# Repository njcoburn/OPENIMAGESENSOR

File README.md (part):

# Open Image Sensor

**Current — completed results checkpoint, 4 October:** all 18 selected
five-device bank cases passed, with 36 transients and 3,456 reference calculations.
The sequence finished 2 October at 15:11 Pacific after 48 h 21 min; no verification
jobs remain active. Worst total/tracking errors are 456.591/215.322 µV against
500 µV; sample refinement is 0.465218 µV against 10 µV. This is selected coverage
of a one-row, 64-column bank, not full-chip qualification.
Next: define bounded supply/wiring/placement checks before real drivers and
multirow integration. [Resume here](PICK_UP_HERE.md) ·
[Completion record](simulations/stack5-completion-checkpoint-20261004.json) ·
[Overview](docs/overview.html#stack5-completion).
Earlier status entries below are historical.

**Latest review, 30 September — stopped; no active simulations:** all three
100 ns runs and 576 references completed and are independently audited. All three
50 ns runs hit the four-hour timeout, leaving 11 of 384 output samples unverified.
Coarse typical/SS totals are 391.959/445.375 µV, but FF is 602.413 µV against
500 µV. 7 available fine FF samples also exceed the limit (up to 577.376 µV).
No complete pair is qualified and the later queue did not start. Next: address
remaining fast-corner capture/storage error and use a longer watchdog for reruns.
[Reviewed evidence](docs/overview.html#stack3-interrupted-review) · [Handoff](PICK_UP_HERE.md).
Earlier running/completion statements below are historical.

**Running, 30 September — 64-column candidate sequence:** checkpoint and
changelog were pushed as `06889e5` before this work. The new physical 64-column
bank passes DRC/LVS and all capture-chain checks. Six typical/SS/FF 125 °C
simulations are running, with 576 matched references planned for this batch.
On audited passes, the controller advances through mixed corners, 27 °C cases,
and remaining typical-process illumination patterns (18 cases / 36 transients /
3,456 references in the complete queue). Failure stops subsequent stages.
[Live overview](docs/overview.html#stack3-sequence) · [Status](build/stack3-sequence-20260930-away/status.json).
Earlier status entries below are historical.

**Latest, 30 September — physical candidate verified:** the three-device capture
switch is implemented in a separate column and two-column bank. DRC/LVS and
40 µm abutment pass. With 12.5 µs acquisition, extracted typical/SS/FF worst total
errors are 152.197/181.071/258.782 µV across port/far placement (limit 500 µV).
Placement sensitivity is below 0.044 µV. This stage completed 18 transients and
108 references. Next: separate 64-column candidate build and process validation.
No simulation jobs remain active; the old 64-column checkpoint is unchanged.
[Physical candidate and rerun guide](docs/overview.html#physical-stack3) · [Handoff](PICK_UP_HERE.md).
Earlier status entries below are historical.

**Latest, 30 September — candidate cycle tests reviewed:** 20 transients and
120 references are complete. Three series NMOS capture devices pass the selected
two-column typical/SS/FF screen; FF error improves from 1240.756 to 410.653 µV
(limit 500 µV). A separate 12.5 µs acquisition test improves SS settling.
Next: check the combined changes, implement a separate physical column revision,
verify extraction/DRC/LVS and small-bank behavior, then repeat full-bank corners.
The current GDS and its known process failures remain unchanged. No jobs are active.
[Results and rerun guide](docs/overview.html#bank-capture-cycles) · [Handoff](PICK_UP_HERE.md).
Earlier status entries below are historical.

**Diagnosis completed, 30 September:** the process failures are reviewed and
short current/candidate tests are complete. FF retention is dominated by the
NMOS capture switch in the probed states; series devices reduce DC leakage but
are not yet a validated correction. Next: candidate capture/readout transients
and an SS acquisition-timing test. No new long batch is active.
[Diagnosis and plots](docs/overview.html#bank-process-diagnosis) · [Handoff](PICK_UP_HERE.md).

**Current, 30 September:** the SS/FF process batch finished. Both total-error
checks fail (512.924 / 2000.323 µV vs 500 µV); other selected checks pass. All
384 references are audited and 1,740 evidence files verify. Next is diagnosis
of SS output settling and FF storage retention, before more corner coverage.
[Review](simulations/compact-bank-process-review-20260930.json) · [Handoff](PICK_UP_HERE.md).
Earlier active-job descriptions below are historical.

**Active, 30 September:** the first SS/FF MOS-process batch is running at
125 °C inverse illumination: four 100/50 ns transients and 384 planned references,
with an independent watcher. The small FF control failed capture/storage accuracy;
that failure is retained while measuring the actual 64-column layout. Results
are pending. [Overview journal](docs/overview.html#verification-journal) ·
[Profile and scope](verification/compact-bank-process-suite.json) · [Handoff](PICK_UP_HERE.md).

[Verification journal and rerun guide](docs/verification-journal.html) explains every test, records results and tracks what is needed for repeatable pixel-layout experiments.

**Completed and reviewed, 30 September:** bright illumination and the authorized
joint parasitic-placement batch both pass. All five illumination patterns now
pass at 27/125 °C: 20 transients and 1,920 independent references, plus four
placement transients and 384 references. Those baseline jobs are complete; the process batch above is active.
Next: process/wire/supply corners and remaining placement/local-supply checks,
then real drivers and repeated rows. Full-chip qualification remains open.
[Completion review](simulations/compact-bank-overnight-review-20260930.json) · [Handoff](PICK_UP_HERE.md).

**Current goal: 64×64 first silicon on wafer.space GF180, with modest frame rate.**
[Completion plan](COMPLETION_PLAN.md) · [Next steps](NEXT_STEPS.md) · [Handoff](PICK_UP_HERE.md)

**Overnight results:** bright total error is 359.158/402.995 µV at 27/125 °C
against 500 µV. Joint relocation of 67 conserved shunts passes at 27 °C
alternating and 125 °C inverse; the largest HOLD/STORE change is 1.527 µV
against 10 µV. Bright and placement took 3.97 and 3.87 hours respectively,
including audits. All ten simulation/audit containers exited successfully.

**Completed and reviewed, 29 September:** uniform dark passes at 27/125 °C:
248.852/411.912 µV worst total error against 500 µV, with four completed transients
and 384 audited references. The batch finished in 4.04 hours. Nothing from this
batch is still running; middle and bright have also passed as described above.
[Uniform results](docs/overview.html#compact-bank-64-uniform).

[View the current device layout](docs/overview.html#current-device-layout) — labeled
GDS and close-up of the implemented 64-column bank plus one pixel row, measuring
2.668 × 1.070 mm. [Exact GDS checkpoint](checkpoints/compact-bank-64-matrix/README.md).
The full 64×64 chip remains to be assembled.

**Latest, reviewed 29 September:** the complete alternating/inverse matrix now
**passes at both 27 °C and 125 °C**. The new 27 °C inverse / 125 °C alternating
cases reach 387.179/430.383 µV worst total error, below 500 µV. All eight matrix
transients and 768 references are audited; maximum saved-sample refinement is
0.150 µV, below 10 µV. All 1,707 distinct new evidence files verify. The jobs and
auditor finished successfully; the completed uniform-dark batch is described above.
[Temperature/pattern matrix](docs/overview.html#compact-bank-64-cross)

**Completed, 28 September:** both earlier complete 64-column bank screens **pass**.
All four transients finish 128 reads each, with 384 independently audited references
across the nominal alternating and hot inverse cases. Worst total error is
**372.606 µV at 27 °C / 438.213 µV at 125 °C**, below 500 µV; maximum saved-sample
100/50 ns difference is **0.133 µV**, below 10 µV. All 1,711 distinct evidence
files verified. The jobs and auditor have finished successfully.

All five illumination patterns at both temperatures now pass. Remaining
corner/placement coverage precedes real drivers and repeated rows.
Full-chip qualification remains open.
[Results and plots](docs/overview.html#compact-bank-64-full) · [Current handoff](PICK_UP_HERE.md)

**Previous electrical results, 27 September:**

The [16-column extension](docs/overview.html#compact-bank-16-extension) passes
its selected checks across **46 transients and 1,152 references**. Worst total
error is 433.171 µV and tracking is 301.667 µV
(500 µV limits). All five patterns at 27/125 °C have 100/50 ns comparisons;
the largest saved-terminal difference is 0.450 µV. All 19 individual
shunts plus their joint placement pass for the hot inverse pattern, with
0.105/0.137 µV maximum HOLD/STORE changes (10 µV limit). The separate
inverse-pattern layout–schematic response reaches 10.062 mV and has
no assigned acceptance threshold.

The 8 µm bus alone does not solve 64-column scaling: a matched column-62
readout fails at 1,994.440 µV total error. A new physical distributed ground
return **fails with 10 µs acquisition** at 547.178 µV total error and
340.253 µV tracking. Both main DRC checks and both LVS paths pass, and
a geometry audit restricts the change to ground metal/vias. The new bank is
2667.87 × 1069.80 µm, within the 2700 × 1100 µm budget. See the
[selected readout comparison](docs/overview.html#compact-bank-64-read-probes)
and [capture/ground diagnosis](docs/compact-bank-64-ground8.md).

Extending acquisition from 10 to 12 µs on that same grid **passes the selected
diagnostic** at 269.281 µV total error and 62.529 µV tracking. Only the
ACQ falling edges and sample times move; selection/reset and the 20 µs slot
budget stay unchanged. Three new matched references and an unchanged-prefix
comparison are audited. The separately versioned full-bank runner now supports
this timing. The original attempts were stopped on 27 September; the resumed
nominal/hot inverse pairs now pass their complete selected audits. See
PICK_UP_HERE.md for results and the next coverage batch.

These are bounded development screens. Full 16-column corner/placement
coverage, remaining full-bank corners/individual placements, real drivers, repeated rows
and exact 64×64 manufacturing qualification remain open.

**Original geometry constraint:** the older array and bank do not fit a standard
full slot. The compact pixel/bank work above addresses that block-size constraint. The new 40 µm-pitch
[floorplan budget](docs/64x64-slot-fit.md) fits the published default core as
planning rectangles; it is not qualified GDS. The full 64×64 chip is not yet assembled.

The extracted 64-pixel row and isolated physical capture column have passing
electrical evidence. The physical bank passes scoped DRC/LVS, but coupled
readout, multirow operation, real drivers and final-chip signoff remain open.
Docker access is restored. The new [40 µm compact pixel](docs/compact-pixel.md)
and 2×2 control pass main DRC and both LVS paths; the 2×2 nominal/hot electrical
screens and timestep checks pass. The [reset follow-up](docs/compact-reset.md)
passes 12 transients and extended references using audited shunt placements;
the raw isolated extraction remains diagnostic. The original raw/reduced full-bank
initialization timed out in four bounded controls before the later KLU
continuation resolved startup. The new [compact capture column](docs/compact-capture.md) fits 40 µm
pitch and passes scoped DRC/LVS, adjacent-column spacing, 60 transients and
36 references. The [physically joined tile](docs/compact-tile.md) now passes
54 transients and 72 references, with 419.404 µV worst total capture/readout
error. The [shared two-column bank](docs/compact-bank.md) now passes both main
DRC/LVS paths, 100 transients and 240 references (419.033 µV worst total error).
It includes physical reference MOS and shared buses; the later 1×64 work is above.
The separate layout–schematic integrated-response difference reaches 5.821 mV.
A separate
3×3 tapeout is not a prerequisite.

## Earlier development checkpoints

The dated entries below retain earlier evidence and historical release targets.
Use the completion plan above for current priorities.

**Latest physical result:** Reinforced supply/reference and local buffer routing passes both main DRC checks and both LVS paths. Worst nominal/hot static buffer shift across 1.2–2.0 V falls from **5.331 to 1.320 mV**; all 16 selected DC controls complete. The coupled reset test still times out during initialization; full readout remains unqualified. [Measured comparison and tradeoffs](docs/bank-reinforcement.md).

**Earlier physical result:** The shared 64-column capture bank passes Magic/KLayout main DRC and both LVS paths: 450 MOS devices, 512 storage plates and fully extracted shared routing. Isolated DC controls reveal millivolt-scale spatial shifts; coupled-row accuracy is not yet qualified. [Bank measurements and scope](docs/capture-bank.md).

**Earlier diagnosis:** Eight DC controls implicate VDD/PREF routing in the spatial spread; idealizing supplies/references still leaves a 2.199 mV common offset. Full readout qualification remains open. [Measured controls and reset diagnostics](docs/bank-routing.md).

**Earlier isolated-column result:** The isolated capture/readout column passes all 48 nominal/hot simulations, Magic/KLayout main DRC and both LVS paths. Worst tracking error is 176.560 µV (limit 500); timestep difference is 0.318 µV (limit 10). Shared-bank results are above. [Qualification and scope](docs/capture-column-qualification.md).

**Latest full-row result:** Full 64-column readout on the physical power grid passes at 27/125 °C: 173.457/289.658 µV total output error (limit 500) and 3.897/3.703 µV timestep difference (limit 10). Pixel/row wiring uses extracted R+C; physical storage/periphery, multirow operation and startup remain open. [Results](docs/grid-readout.md) · [Next physical tile](docs/capture-tile-plan.md).

**Earlier grid result:** A physical upper-metal row power grid reduces turn-on VDD loss from 354.35 to 42.57 mV, with passing layout/connectivity checks and nominal edge refinement. Nominal/hot runs complete through capture at about 4.09 mV wiring loss. The full serial-output follow-up is now complete; see the latest result above. [Measurements and scope](docs/row-power.md).

**Earlier capture result:** The revised 64-column capture circuit passes nominal/hot accuracy and timestep checks: 171.295/289.919 µV total error, below 500 µV. It removes the measured serial-exposure gradient in these tests. Physical capacitors, distributed power and peripheral routing remain the next stage; startup/full-chip/tapeout qualification is open. [Results and exact scope](docs/array-recovery.md).

**Earlier strip result:** Extracted 1×64/64×1 tests exposed supply drop, exposure skew and late bright-pixel saturation. The original serial mode's numerical refinement remains unqualified. [Original measurements](docs/array-strips.md).

**Earlier interface result:** The proposed heavy-load interface completes three frames at 0.461 mV tracking error. Explicit unused-pad terminations allow both cold cases to run, including a selected three-frame/refinement check. These are conditional proposals, not released hardware. [Results](docs/readout-followup.md) · [Are we ready for tapeout or a larger array?](docs/tapeout-readiness.md).

**Earlier load/corner screen:** Five initial load/corner conditions pass; heavier capacitive loads miss the existing acquisition-time margin, and two cold corners remain blocked at DC. The 100 kΩ load also has a completed three-frame check. [Results and exact coverage](docs/camera-operating-corners.md).

**Previous nominal result:** Three full-camera frames complete with 27 samples. Frame-two/three drift is 5.733 µV, and matching DC readout references are checked. [Results and exact scope](docs/three-frames.md).

**Standalone rows:** All three rows have identical local devices, and all 12 standalone reset tests complete—including pad protection, finite supply and finer-step controls. These earlier isolated tests led into the successful staged/full-frame follow-up. [Step-by-step row report](docs/standalone-row.md).

**Earlier frame attempt:** Explicit solver abort at 3.27002 ms after 21.06 minutes; six pixels retained, third row missing. [Results and failure plots](docs/streamed-frame.md). The instrumented rerun reproduces the failure exactly; isolated row tests are described above.

**Switching diagnostic:** The unchanged candidate crosses the previously reported row-turn-off stall and completes through 3.24 ms. Streaming capture retains six pixel samples; no complete frame or fabrication pass is claimed. [Results and plots](docs/functional-camera-diagnostic.md).

**Simulator comparison:** matched ngspice 46/47 controls pass, but both extracted stock-model tests fail at startup. Upgrade alone is insufficient; a separate v47 multiplier parser failure has a minimal public issue draft. [Results](docs/ngspice-version-comparison.md).

**Electrical qualification update:** Final-chip lumped capacitance and charge-preserving fill reduction are checked. Stricter pad-corner simulations still fail at the clamp load transition; complete-chip electrical qualification is **not yet passed**. [Results and next steps](docs/scaled-electrical-progress.md).

## Electrical qualification update — 2026-09-19 09:34 PDT

[New control-resolution and extracted-clamp results](docs/scaled-electrical-progress.md): matched capacitor controls pass the unchanged current limit; the isolated extracted clamp completes and passes 25 ns/tolerance voltage refinement. Both complete-corner capacitance placements now complete at 50 ns. These are diagnostic milestones, **not complete-chip qualification**. Final-GDS extraction and the [remaining electrical gates](docs/full-chip-electrical-plan.md) are open.

## Removable sensor tester — KiCad prototype

[KiCad projects and Windows instructions](hardware/carrier/README.md) · [Illustrated overview](docs/carrier-fixture.html) · [Download review ZIP](hardware/carrier/openimagesensor-kicad-review.zip)

40 × 40 mm removable carrier, underside pogo contacts and an ADS1115 tester. Both PCBs pass the current native DRC and pin/net comparison. Electrical, mechanical and wire-bond reviews remain open; this is not a fabrication release.

**Path to a working camera — 19 September 2026:** [Finish the 3×3, characterize the photodiodes, then scale to 64×64](docs/path-to-camera.md). Carrier/interface and manufacturing planning can proceed alongside the clamp-model review.

## Current completion checkpoint — 19 September 2026

**First release: 3×3.** The core has earlier passing checks; the assembled chip is not fabrication-ready. A new evidence-backed numerical candidate passes isolated-clamp voltage refinement and completes both corner-placement transients; the final-chip electrical tests remain open. The working pad arrangement now has verified routing and central fill; density, antenna, main DRC and device LVS pass. Electrical and manufacturing qualification remain open.

**Electrical blocker explained:** [local clamp-model review](docs/clamp-model-review.md). The original failure and subsequent control-resolution findings are documented; the candidate is not yet an accepted full-chip fix. No external expert has yet reviewed the packet.

[Completion plan](COMPLETION_PLAN.md) · [Pins and board interface](docs/demonstrator-interface.md) · [Unsent expert-review package](docs/reviews/clamp-startup-review.md) · [Manufacturing questions](docs/manufacturing-review.md)

Historical diagnostic checkpoints below retain their original scope and limitations.

**MOS-capacitor diagnosis (2026-09-19 01:49 PDT):** 24/24 simple capacitor transients complete; 0/4 initial isolated-clamp transients complete. Integration follow-up: 1/2 complete; refinement: 0/2 pass. [Report and plots](docs/moscap-branch.md).

**Latest simulation check (2026-09-19 01:32 PDT):** DC/AC interface comparison: NOT VERIFIED. Full-corner ramp/load transients: NOT VERIFIED. [Details](docs/corner-interface.md).

An open monochrome image-sensor experiment using GF180MCU, Xschem,
ngspice, gdsfactory, Magic, KLayout, and Netgen.

**Project checkpoint: 18 September 2026** · [Changelog](CHANGELOG.md) · [Dated next steps and handoff](NEXT_STEPS.md) · [Engineering notebook](docs/overview.html)

## First release: a 3×3 monochrome demonstrator

The active target is **nine pixels with external timing and an external ADC**. The core layout and earlier electrical checks exist; functional signal-pad routing is implemented in a working candidate; full-chip verification and optical packaging remain open.

**Current plan:** [completion milestones and stop rule](COMPLETION_PLAN.md) · [logical pins and board interface](docs/demonstrator-interface.md) · [manufacturing questions](docs/manufacturing-review.md) · [simulator review package](docs/reviews/clamp-startup-review.md).

Signal path: light → pixel → column bias/multiplexer → shared buffer → signal pad → board ADC → controller. The earlier power-only vehicle is superseded by the separate routed working-layout checkpoint below.

### Filled layout: density and antenna checked

Regenerated central fill with all nine optical keepouts preserved. Density/antenna and main KLayout DRC report zero violations; device LVS matches uniquely; all 4,566 connectivity checks pass. [Verification report](docs/filled-demonstrator.md) · [HTML overview](docs/overview.html#filled-demonstrator). Full-chip electrical qualification and run-specific manufacturing checks remain open.

### Routed working layout

13 functional signal paths routed through local protection; seven supply/return pads connected. Metal connectivity: 4566 checks, PASS. Main KLayout DRC: 0 markers. Magic DRC: 0. Device LVS unique match: True. The four diagnostic signal paths remain disconnected. Final fill, manufacturing and electrical sign-off remain open. [Verification report](docs/routed-demonstrator.md).

### Provisional pad-placement review

Original placement-only concept, now approved for local implementation: 19 core nets, 24 pads. See the newer routed checkpoint above. Die outline and optical packaging remain open. [Pad table and review gates](docs/pad-proposal.md) · [Coordinate CSV](docs/proposed-pad-map.csv).

### Later expansion: 64×64 camera concept

This is a future concept, not part of the first release or a routed and verified chip. Earlier area estimates do not establish manufacturing or packaging acceptance.

## 3×3 verification: reduced RC and placement sensitivity

Four resistor reductions pass numerical and DC checks. Full corner: 571,551 → 87,748 resistors; metal-only corner: 451,892 → 12. Placement sensitivity is now measured in coupon fixtures, with numerical and startup limits retained. [Results](docs/charge-reduction.md).

## 3×3 release: charge-conserving RC reference

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
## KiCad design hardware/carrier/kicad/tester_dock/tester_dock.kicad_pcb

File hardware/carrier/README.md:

# KiCad removable sensor fixture — revision A

Prepared 19 September 2026. Two editable **KiCad 7** projects implement the provisional 40 × 40 mm carrier and a tester with an optical aperture. **Engineering review prototype; not released for fabrication.**

## Open on Windows

Your existing KiCad installation is sufficient (KiCad 7 or newer). Copy the entire `hardware/carrier` folder to Windows, or extract the accompanying `openimagesensor-kicad-review.zip`. Open these project files from KiCad's **File → Open Existing Project**:

- [Tester dock](kicad/tester_dock/tester_dock.kicad_pro) — ADC, buffers, supply input, controller headers and underside pogo contacts.
- [Removable die carrier](kicad/die_carrier/die_carrier.kicad_pro) — die bond template, contact targets and local bias components.

Then open the schematic or PCB from the project manager. Embedded schematic symbols and each project's `OIS.pretty` footprint library travel with the files. Preserve `fp-lib-table` and the footprint folders. If accessing the checkout directly from Windows, its WSL path is `\\wsl.localhost\<your-distribution>\home\njcoburn\code\OPENIMAGESENSOR\hardware\carrier`; otherwise copy/extract to an ordinary Windows folder.

## Design overview

The dock sits above the carrier; the upward-facing die is visible through a 22 × 22 mm opening. Four screws use a 32 mm square mounting pattern. A round locating hole and an asymmetrically placed slot provide registration when mating locating hardware is fitted. The drawings retain a common top-view coordinate system.

- [Assembly, mechanics and bring-up](ASSEMBLY.md)
- [ADS1115 evaluation and slow-readout proposal](ADC.md)
- [Exact mechanical coordinates](kicad/mechanical.json)
- [Die connection specification](die-connections.csv) and [controller header](controller-header.csv)
- Schematic PDFs: [dock](reports/tester_dock-schematic.pdf), [carrier](reports/die_carrier-schematic.pdf)
- Native check summary: [checks.json](reports/checks.json); full DRC: [dock](reports/tester_dock-drc.txt), [carrier](reports/die_carrier-drc.txt)

ADS1115 is included for slow measurements. It cannot follow the existing 18 µs column slots. The pixel continues integrating during its approximately 1.16 ms conversion at the highest rate; the slow acquisition sequence needs validation. J4 exposes a buffered analog path for evaluating a faster ADC. No microcontroller or firmware is selected yet.

**P03 and P08 contact positions are reserved/unconnected at the interface.** BIAS and PREF resistors reside on the carrier and connect directly to their die bond fingers. P10/P11/P12/P15 remain unused. This avoids taking the high-impedance bias node through a spring contact.

## Reproduce with Docker

Windows KiCad does not need Docker. The isolated Linux toolchain is provided to regenerate and check these files:

```bash
docker build -t openimagesensor-kicad:7 tools/kicad
bash scripts/run-kicad.sh python3 hardware/carrier/generate_kicad.py
bash scripts/run-kicad.sh python3 hardware/carrier/route_kicad.py tester_dock
bash scripts/run-kicad.sh python3 hardware/carrier/route_kicad.py die_carrier
bash scripts/run-kicad.sh python3 hardware/carrier/check_kicad.py
bash scripts/run-kicad.sh python3 hardware/carrier/clean_kicad.py
bash scripts/run-kicad.sh python3 hardware/carrier/check_kicad.py
bash scripts/run-kicad.sh python3 hardware/carrier/render_kicad.py
```

Run from the repository root. **Generation overwrites the generated projects**; preserve manual edits before using it. Routing requires freshly generated boards and deliberately refuses to overwrite existing routing. The base Ubuntu image is digest-pinned; the installed package version used here is KiCad 7.0.11. Apt packages are not snapshot-pinned, so record the version if rebuilding later.

The checker exports the actual schematic netlist, compares its pin connections with the board, and runs native KiCad DRC. It writes findings even when DRC fails; inspect the reports. KiCad 7's CLI does not supply schematic ERC here: run ERC in Windows KiCad and review the results. Net-name agreement is not a simulation or a substitute for electrical review.

## Verification checkpoint

Native KiCad 7.0.11 reports **zero DRC violations, zero unconnected pads and zero footprint errors** on both boards. The schematic/PCB pin-net comparison matches 186 connected dock pins and 44 carrier pins. Reports include the exact checked file hashes. No schematic ERC or board electrical simulation has been completed.

## Remaining release work

1. Run GUI ERC and inspect both boards in 3D; repeat native DRC after any edits.
2. Review return paths/ground planes, bypass placement, output stability, power sequencing and slow ADC timing. The current four-layer route is an initial connectivity layout, not an analog performance qualification.
3. Confirm the spring-contact drawing and full spacer/board tolerance stack, then get a wire-bond provider's approval of die attach, finger geometry, finish and loop height.
4. Select the controller, implement a timed single-pixel bench mode, and qualify the dock without a die before attaching a carrier.
5. Continue the separate chip clamp-model review. The PCB does not resolve that full-chip simulation limitation.

No Gerbers, purchasing order or fabrication release is supplied. Nothing needs to be installed on your Windows machine beyond KiCad to review this checkpoint.

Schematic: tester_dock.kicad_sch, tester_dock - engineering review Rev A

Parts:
C1, C2, C3, C5: 100n; Capacitor_SMD_C_0805_2012Metric
C4, C7: 10n; Capacitor_SMD_C_0805_2012Metric
C6: 1u; Capacitor_SMD_C_0805_2012Metric
C8: 10u; Capacitor_SMD_C_0805_2012Metric
J1: CONTROLLER_TIMING; Connector_PinHeader_2.54mm_PinHeader_2x10_P2.54mm_Vertical
J2: 3V3_INPUT_ONLY; Connector_PinHeader_2.54mm_PinHeader_1x02_P2.54mm_Vertical
J3: I2C_AND_ENABLE; Connector_PinHeader_2.54mm_PinHeader_1x06_P2.54mm_Vertical
J4: FAST_ADC_ANALOG; Connector_PinHeader_2.54mm_PinHeader_1x03_P2.54mm_Vertical
P1, P2, P3, P4, P5, P6, P7, P8, P9, P10, P11, P12, P13, P14, P15, P16, P17, P18, P19, P20, P21, P22, P23, P24: 0906-0-15-20-76-14-11-0; Pogo_0906_0
R1, R2, R3, R4, R5, R6, R7, R8, R9, R24, R25: 100; Resistor_SMD_R_0805_2012Metric
R11, R12, R13, R14, R15, R16, R17, R18, R19, R31, R32, R33, R34, R35, R36, R37, R38, R39: 100k; Resistor_SMD_R_0805_2012Metric
R21: 10k; Resistor_SMD_R_0805_2012Metric
R22: 13k 0.1%; Resistor_SMD_R_0805_2012Metric
R23: 20k 0.1%; Resistor_SMD_R_0805_2012Metric
R26, R27, R28: 4.7k; Resistor_SMD_R_0805_2012Metric
U1, U2: SN74LVC244APW; Package_SO_TSSOP-20_4.4x6.5mm_P0.65mm
U3: OPA2320AID; Package_SO_SOIC-8_3.9x4.9mm_P1.27mm
U4: ADS1115IDGSR; Package_SO_VSSOP-10_3x3mm_P0.5mm

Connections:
ADC_IN: C7.1, R24.2, U4.4 (AIN0)
ADC_RDY: J3.5, R28.1, U4.2 (ALERT_RDY)
BUF: P9.1, U3.3 (IN+_A)
BUF_DRV: R24.1, R25.1, U3.1 (OUT_A), U3.2 (IN-_A)
CTL_ROW0: J1.7, R34.1, U1.8 (1A4)
CTL_ROW1: J1.9, R35.1, U1.11 (2A1)
CTL_ROW2: J1.11, R36.1, U1.13 (2A2)
CTL_RST0: J1.1, R31.1, U1.2 (1A1)
CTL_RST1: J1.3, R32.1, U1.4 (1A2)
CTL_RST2: J1.5, R33.1, U1.6 (1A3)
CTL_SEL0: J1.13, R37.1, U1.15 (2A3)
CTL_SEL1: J1.15, R38.1, U1.17 (2A4)
CTL_SEL2: J1.17, R39.1, U2.2 (1A1)
DRV_ROW0: R4.1, U1.12 (1Y4)
DRV_ROW1: R5.1, U1.9 (2Y1)
DRV_ROW2: R6.1, U1.7 (2Y2)
DRV_RST0: R1.1, U1.18 (1Y1)
DRV_RST1: R2.1, U1.16 (1Y2)
DRV_RST2: R3.1, U1.14 (1Y3)
DRV_SEL0: R7.1, U1.5 (2Y3)
DRV_SEL1: R8.1, U1.3 (2Y4)
DRV_SEL2: R9.1, U2.18 (1Y1)
FAST_OUT: J4.1, R25.2
GND: C1.2, C2.2, C3.2, C4.2, C5.2, C6.2, C7.2, C8.2, J1.2, J1.4, J1.6, J1.8, J1.10, J1.12, J1.14, J1.16, J1.18, J1.20, J2.2, J3.2, J4.2, P1.1, P7.1, P13.1, P19.1, R14.2, R15.2, R16.2, R17.2, R18.2, R19.2, R23.2, R31.2, R32.2, R33.2, R34.2, R35.2, R36.2, R37.2, R38.2, R39.2, U1.10 (GND), U2.4 (1A2), U2.6 (1A3), U2.8 (1A4), U2.10 (GND), U2.11 (2A1), U2.13 (2A2), U2.15 (2A3), U2.17 (2A4), U3.4 (V-), U4.1 (ADDR), U4.3 (GND), U4.5 (AIN1), U4.6 (AIN2), U4.7 (AIN3)
IO_OE_N: J3.6, R21.1, U1.1 (1OE_N), U1.19 (2OE_N), U2.1 (1OE_N), U2.19 (2OE_N)
RESET_DIV: C4.1, R22.2, R23.1, U3.5 (IN+_B)
ROW0: P23.1, R4.2, R14.1
ROW1: P21.1, R5.2, R15.1
ROW2: P17.1, R6.2, R16.1
RST0: P22.1, R1.2, R11.1
RST1: P20.1, R2.2, R12.1
RST2: P16.1, R3.2, R13.1
SCL: J3.4, R27.1, U4.10 (SCL)
SDA: J3.3, R26.1, U4.9 (SDA)
SEL0: P4.1, R7.2, R17.1
SEL1: P5.1, R8.2, R18.1
SEL2: P6.1, R9.2, R19.1
VDD: C1.1, C2.1, C3.1, C5.1, C6.1, C8.1, J1.19, J2.1, J3.1, P2.1, P14.1, P24.1, R11.2, R12.2, R13.2, R21.2, R22.1, R26.2, R27.2, R28.2, U1.20 (VCC), U2.20 (VCC), U3.8 (V+), U4.8 (VDD)
VRESET: J4.3, P18.1, U3.6 (IN-_B), U3.7 (OUT_B)

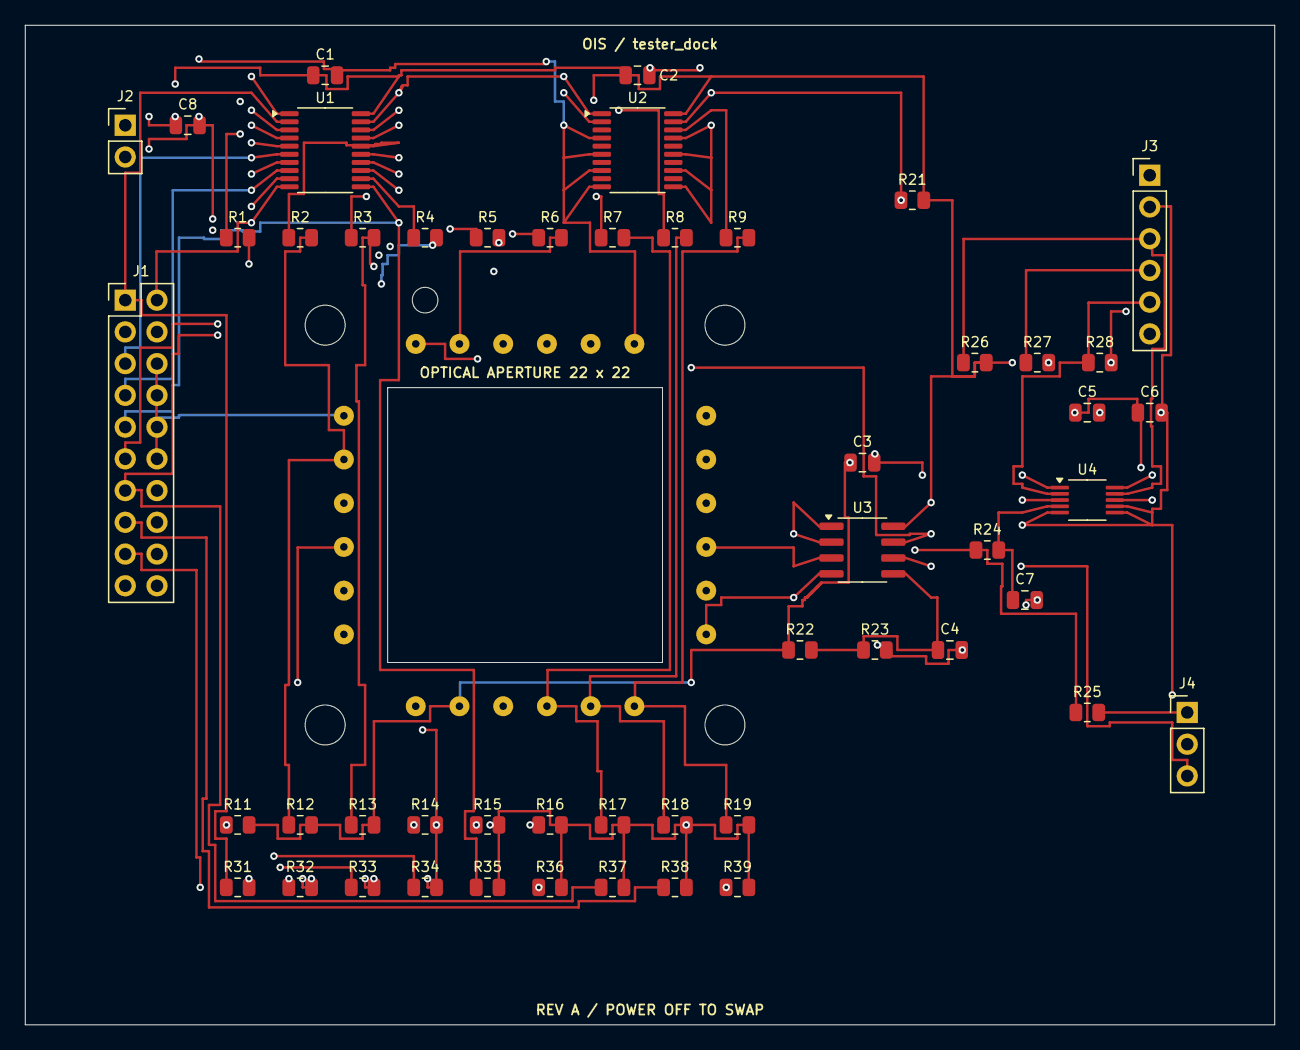
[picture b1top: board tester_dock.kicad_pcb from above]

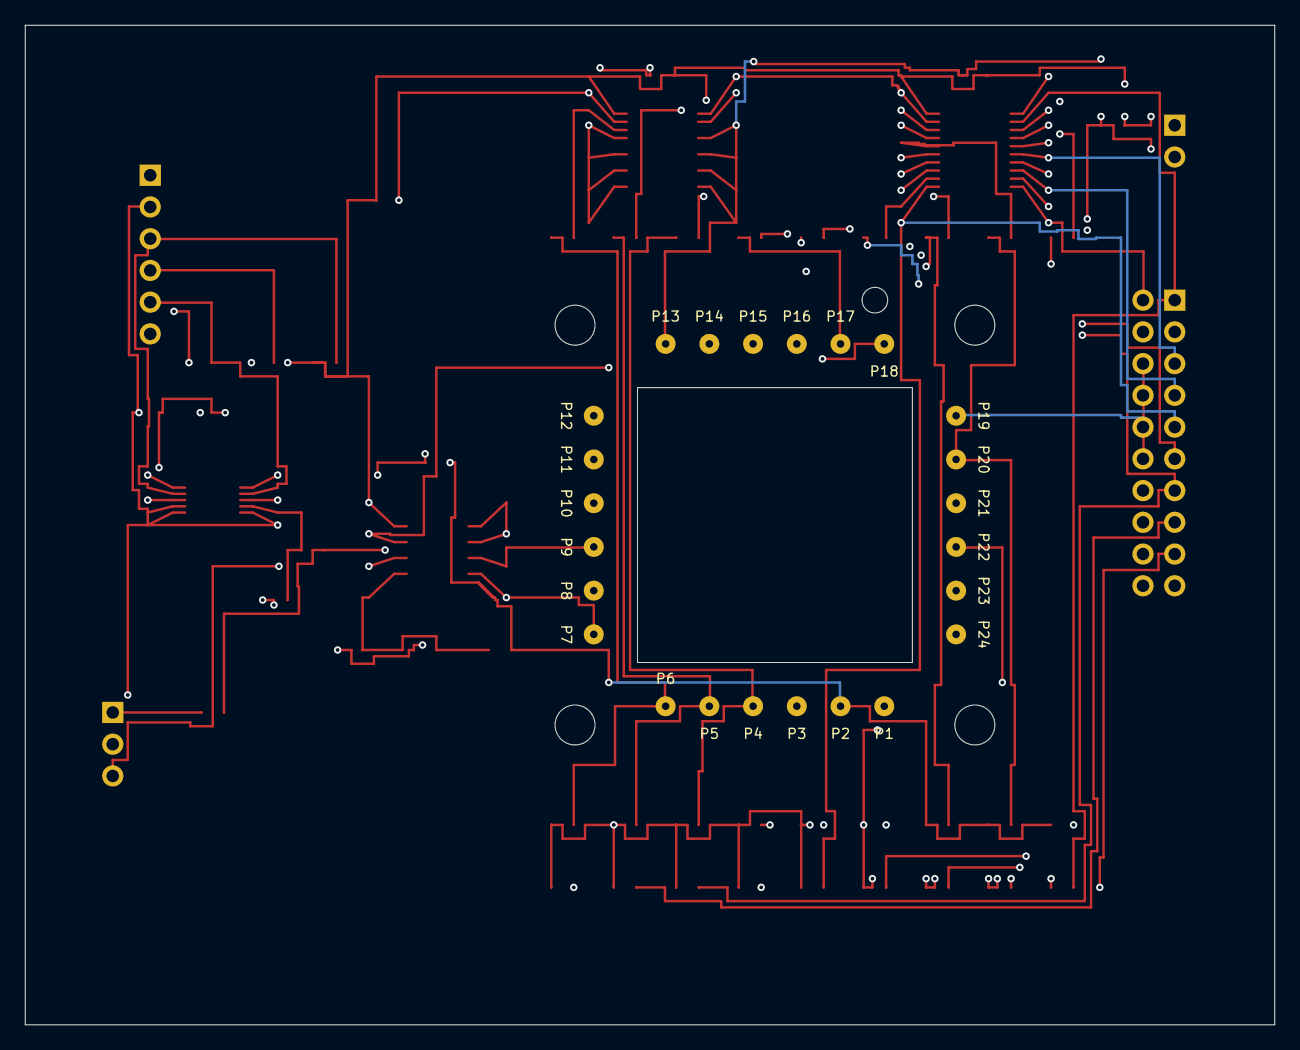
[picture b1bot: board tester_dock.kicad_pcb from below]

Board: 4 copper layers, 100.0 x 80.0 mm, 81 parts (24 on the bottom side), 39 nets.

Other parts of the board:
H1: M3 clearance; Mechanical_1
H2: M3 clearance; Mechanical_2
H3: M3 clearance; Mechanical_3
H4: M3 clearance; Mechanical_4
H5: Alignment round; Mechanical_5
H6: Alignment slot; Mechanical_6

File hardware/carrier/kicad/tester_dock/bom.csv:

Reference,Value_or_MPN,Footprint,Note
P1,0906-0-15-20-76-14-11-0,OIS:Pogo_0906_0,Bottom-facing spring; compression height must be confirmed
P2,0906-0-15-20-76-14-11-0,OIS:Pogo_0906_0,Bottom-facing spring; compression height must be confirmed
P3,0906-0-15-20-76-14-11-0,OIS:Pogo_0906_0,Bottom-facing spring; compression height must be confirmed
P4,0906-0-15-20-76-14-11-0,OIS:Pogo_0906_0,Bottom-facing spring; compression height must be confirmed
P5,0906-0-15-20-76-14-11-0,OIS:Pogo_0906_0,Bottom-facing spring; compression height must be confirmed
P6,0906-0-15-20-76-14-11-0,OIS:Pogo_0906_0,Bottom-facing spring; compression height must be confirmed
P7,0906-0-15-20-76-14-11-0,OIS:Pogo_0906_0,Bottom-facing spring; compression height must be confirmed
P8,0906-0-15-20-76-14-11-0,OIS:Pogo_0906_0,Bottom-facing spring; compression height must be confirmed
P9,0906-0-15-20-76-14-11-0,OIS:Pogo_0906_0,Bottom-facing spring; compression height must be confirmed
P10,0906-0-15-20-76-14-11-0,OIS:Pogo_0906_0,Bottom-facing spring; compression height must be confirmed
P11,0906-0-15-20-76-14-11-0,OIS:Pogo_0906_0,Bottom-facing spring; compression height must be confirmed
P12,0906-0-15-20-76-14-11-0,OIS:Pogo_0906_0,Bottom-facing spring; compression height must be confirmed
P13,0906-0-15-20-76-14-11-0,OIS:Pogo_0906_0,Bottom-facing spring; compression height must be confirmed
P14,0906-0-15-20-76-14-11-0,OIS:Pogo_0906_0,Bottom-facing spring; compression height must be confirmed
P15,0906-0-15-20-76-14-11-0,OIS:Pogo_0906_0,Bottom-facing spring; compression height must be confirmed
P16,0906-0-15-20-76-14-11-0,OIS:Pogo_0906_0,Bottom-facing spring; compression height must be confirmed
P17,0906-0-15-20-76-14-11-0,OIS:Pogo_0906_0,Bottom-facing spring; compression height must be confirmed
P18,0906-0-15-20-76-14-11-0,OIS:Pogo_0906_0,Bottom-facing spring; compression height must be confirmed
P19,0906-0-15-20-76-14-11-0,OIS:Pogo_0906_0,Bottom-facing spring; compression height must be confirmed
P20,0906-0-15-20-76-14-11-0,OIS:Pogo_0906_0,Bottom-facing spring; compression height must be confirmed
P21,0906-0-15-20-76-14-11-0,OIS:Pogo_0906_0,Bottom-facing spring; compression height must be confirmed
P22,0906-0-15-20-76-14-11-0,OIS:Pogo_0906_0,Bottom-facing spring; compression height must be confirmed
P23,0906-0-15-20-76-14-11-0,OIS:Pogo_0906_0,Bottom-facing spring; compression height must be confirmed
P24,0906-0-15-20-76-14-11-0,OIS:Pogo_0906_0,Bottom-facing spring; compression height must be confirmed
J1,CONTROLLER_TIMING,OIS:Connector_PinHeader_2.54mm_PinHeader_2x10_P2.54mm_Vertical,
J2,3V3_INPUT_ONLY,OIS:Connector_PinHeader_2.54mm_PinHeader_1x02_P2.54mm_Vertical,Regulated current-limited 3.3 V bench source; no onboard regulator
J3,I2C_AND_ENABLE,OIS:Connector_PinHeader_2.54mm_PinHeader_1x06_P2.54mm_Vertical,
J4,FAST_ADC_ANALOG,OIS:Connector_PinHeader_2.54mm_PinHeader_1x03_P2.54mm_Vertical,Analog expansion; no 50-ohm termination; external ADC requires load review
U1,SN74LVC244APW,OIS:Package_SO_TSSOP-20_4.4x6.5mm_P0.65mm,
C1,100n,OIS:Capacitor_SMD_C_0805_2012Metric,
U2,SN74LVC244APW,OIS:Package_SO_TSSOP-20_4.4x6.5mm_P0.65mm,
C2,100n,OIS:Capacitor_SMD_C_0805_2012Metric,
R1,100,OIS:Resistor_SMD_R_0805_2012Metric,
R11,100k,OIS:Resistor_SMD_R_0805_2012Metric,
R31,100k,OIS:Resistor_SMD_R_0805_2012Metric,
R2,100,OIS:Resistor_SMD_R_0805_2012Metric,
R12,100k,OIS:Resistor_SMD_R_0805_2012Metric,
R32,100k,OIS:Resistor_SMD_R_0805_2012Metric,
R3,100,OIS:Resistor_SMD_R_0805_2012Metric,
R13,100k,OIS:Resistor_SMD_R_0805_2012Metric,
R33,100k,OIS:Resistor_SMD_R_0805_2012Metric,
R4,100,OIS:Resistor_SMD_R_0805_2012Metric,
R14,100k,OIS:Resistor_SMD_R_0805_2012Metric,
R34,100k,OIS:Resistor_SMD_R_0805_2012Metric,
R5,100,OIS:Resistor_SMD_R_0805_2012Metric,
R15,100k,OIS:Resistor_SMD_R_0805_2012Metric,
R35,100k,OIS:Resistor_SMD_R_0805_2012Metric,
R6,100,OIS:Resistor_SMD_R_0805_2012Metric,
R16,100k,OIS:Resistor_SMD_R_0805_2012Metric,
R36,100k,OIS:Resistor_SMD_R_0805_2012Metric,
R7,100,OIS:Resistor_SMD_R_0805_2012Metric,
R17,100k,OIS:Resistor_SMD_R_0805_2012Metric,
R37,100k,OIS:Resistor_SMD_R_0805_2012Metric,
R8,100,OIS:Resistor_SMD_R_0805_2012Metric,
R18,100k,OIS:Resistor_SMD_R_0805_2012Metric,
R38,100k,OIS:Resistor_SMD_R_0805_2012Metric,
R9,100,OIS:Resistor_SMD_R_0805_2012Metric,
R19,100k,OIS:Resistor_SMD_R_0805_2012Metric,
R39,100k,OIS:Resistor_SMD_R_0805_2012Metric,
R21,10k,OIS:Resistor_SMD_R_0805_2012Metric,
U3,OPA2320AID,OIS:Package_SO_SOIC-8_3.9x4.9mm_P1.27mm,
R22,13k 0.1%,OIS:Resistor_SMD_R_0805_2012Metric,
R23,20k 0.1%,OIS:Resistor_SMD_R_0805_2012Metric,
C3,100n,OIS:Capacitor_SMD_C_0805_2012Metric,
C4,10n,OIS:Capacitor_SMD_C_0805_2012Metric,
U4,ADS1115IDGSR,OIS:Package_SO_VSSOP-10_3x3mm_P0.5mm,
C5,100n,OIS:Capacitor_SMD_C_0805_2012Metric,
C6,1u,OIS:Capacitor_SMD_C_0805_2012Metric,
R24,100,OIS:Resistor_SMD_R_0805_2012Metric,
C7,10n,OIS:Capacitor_SMD_C_0805_2012Metric,
R25,100,OIS:Resistor_SMD_R_0805_2012Metric,
R26,4.7k,OIS:Resistor_SMD_R_0805_2012Metric,
R27,4.7k,OIS:Resistor_SMD_R_0805_2012Metric,
R28,4.7k,OIS:Resistor_SMD_R_0805_2012Metric,
C8,10u,OIS:Capacitor_SMD_C_0805_2012Metric,

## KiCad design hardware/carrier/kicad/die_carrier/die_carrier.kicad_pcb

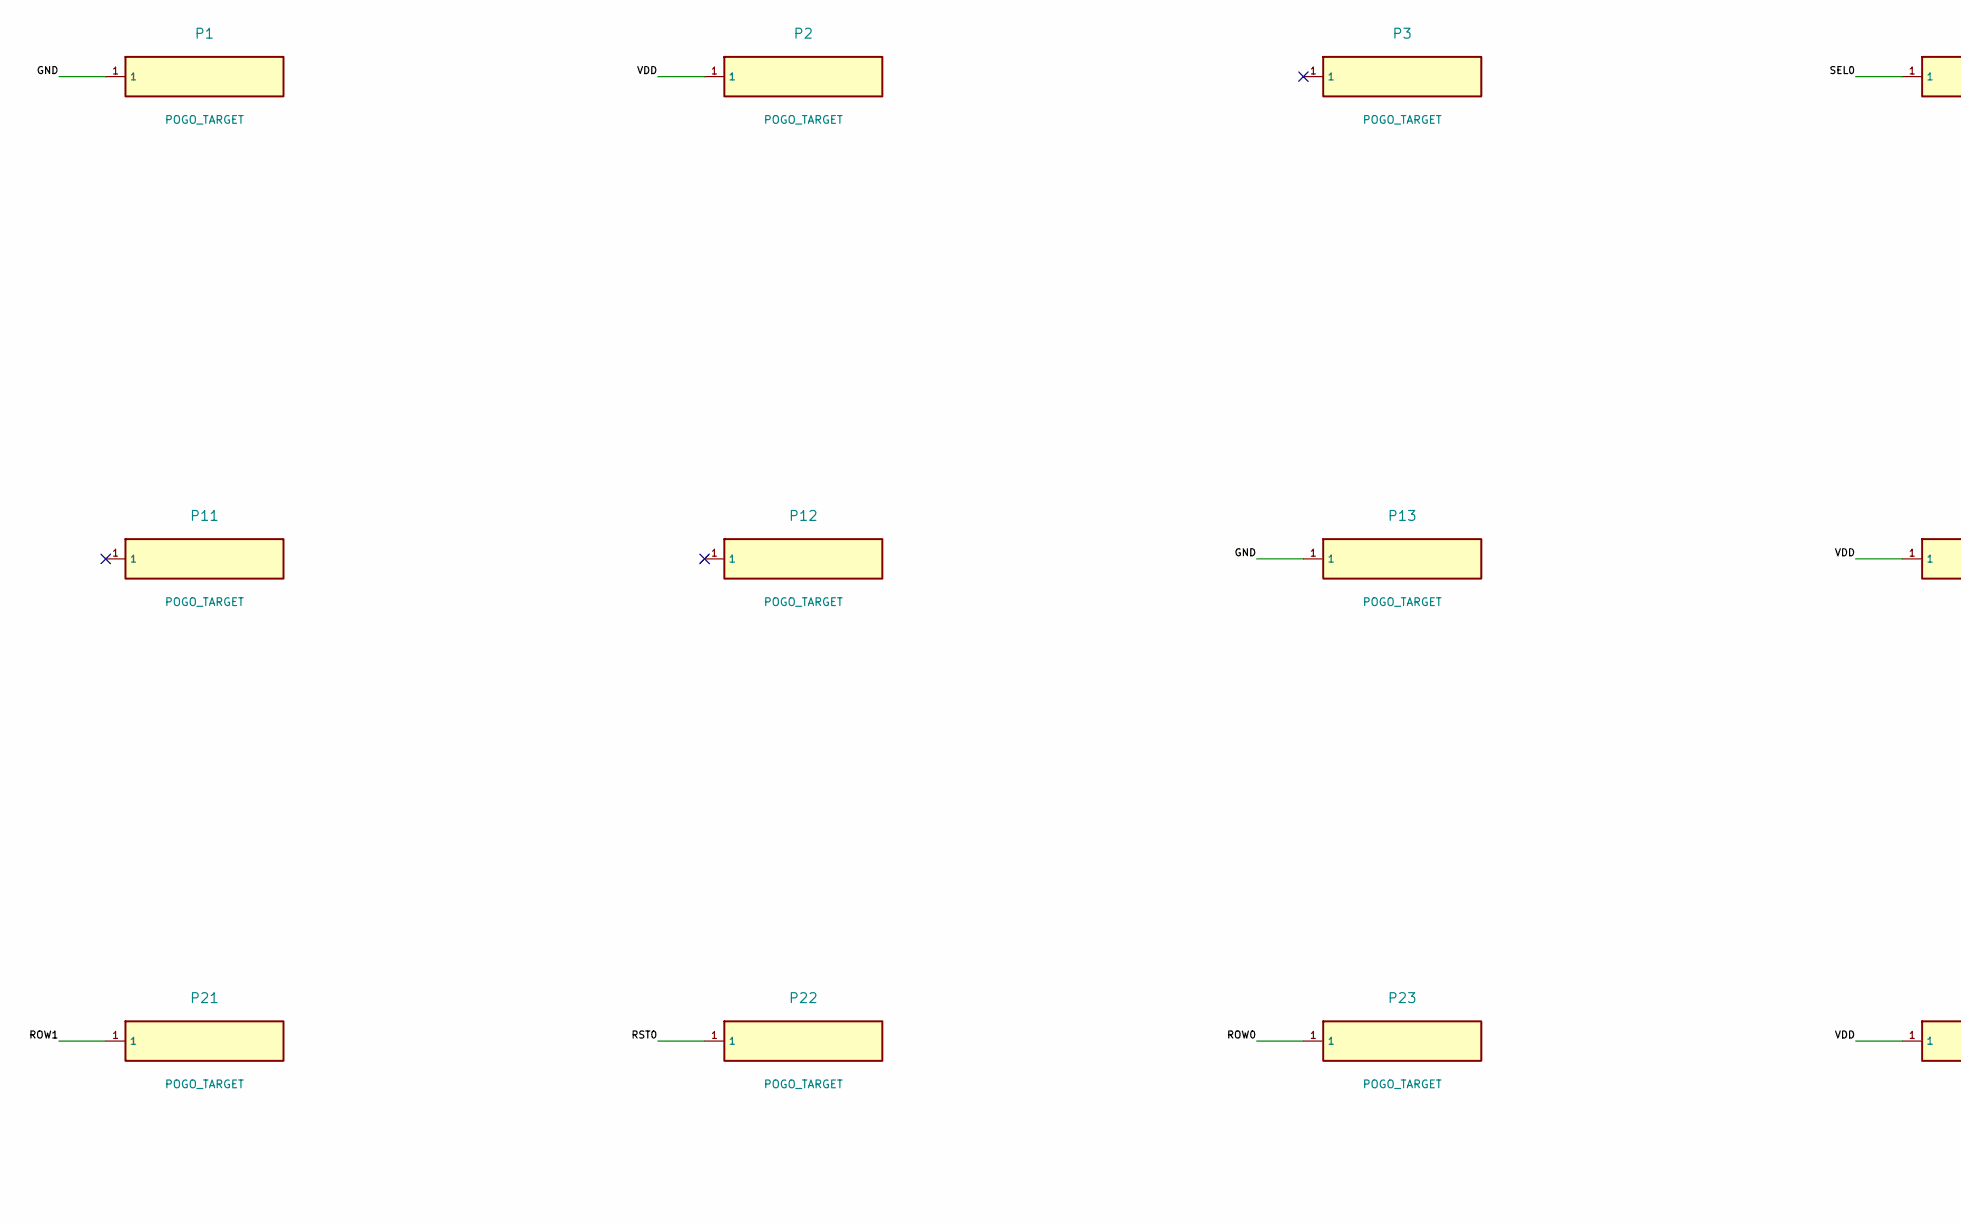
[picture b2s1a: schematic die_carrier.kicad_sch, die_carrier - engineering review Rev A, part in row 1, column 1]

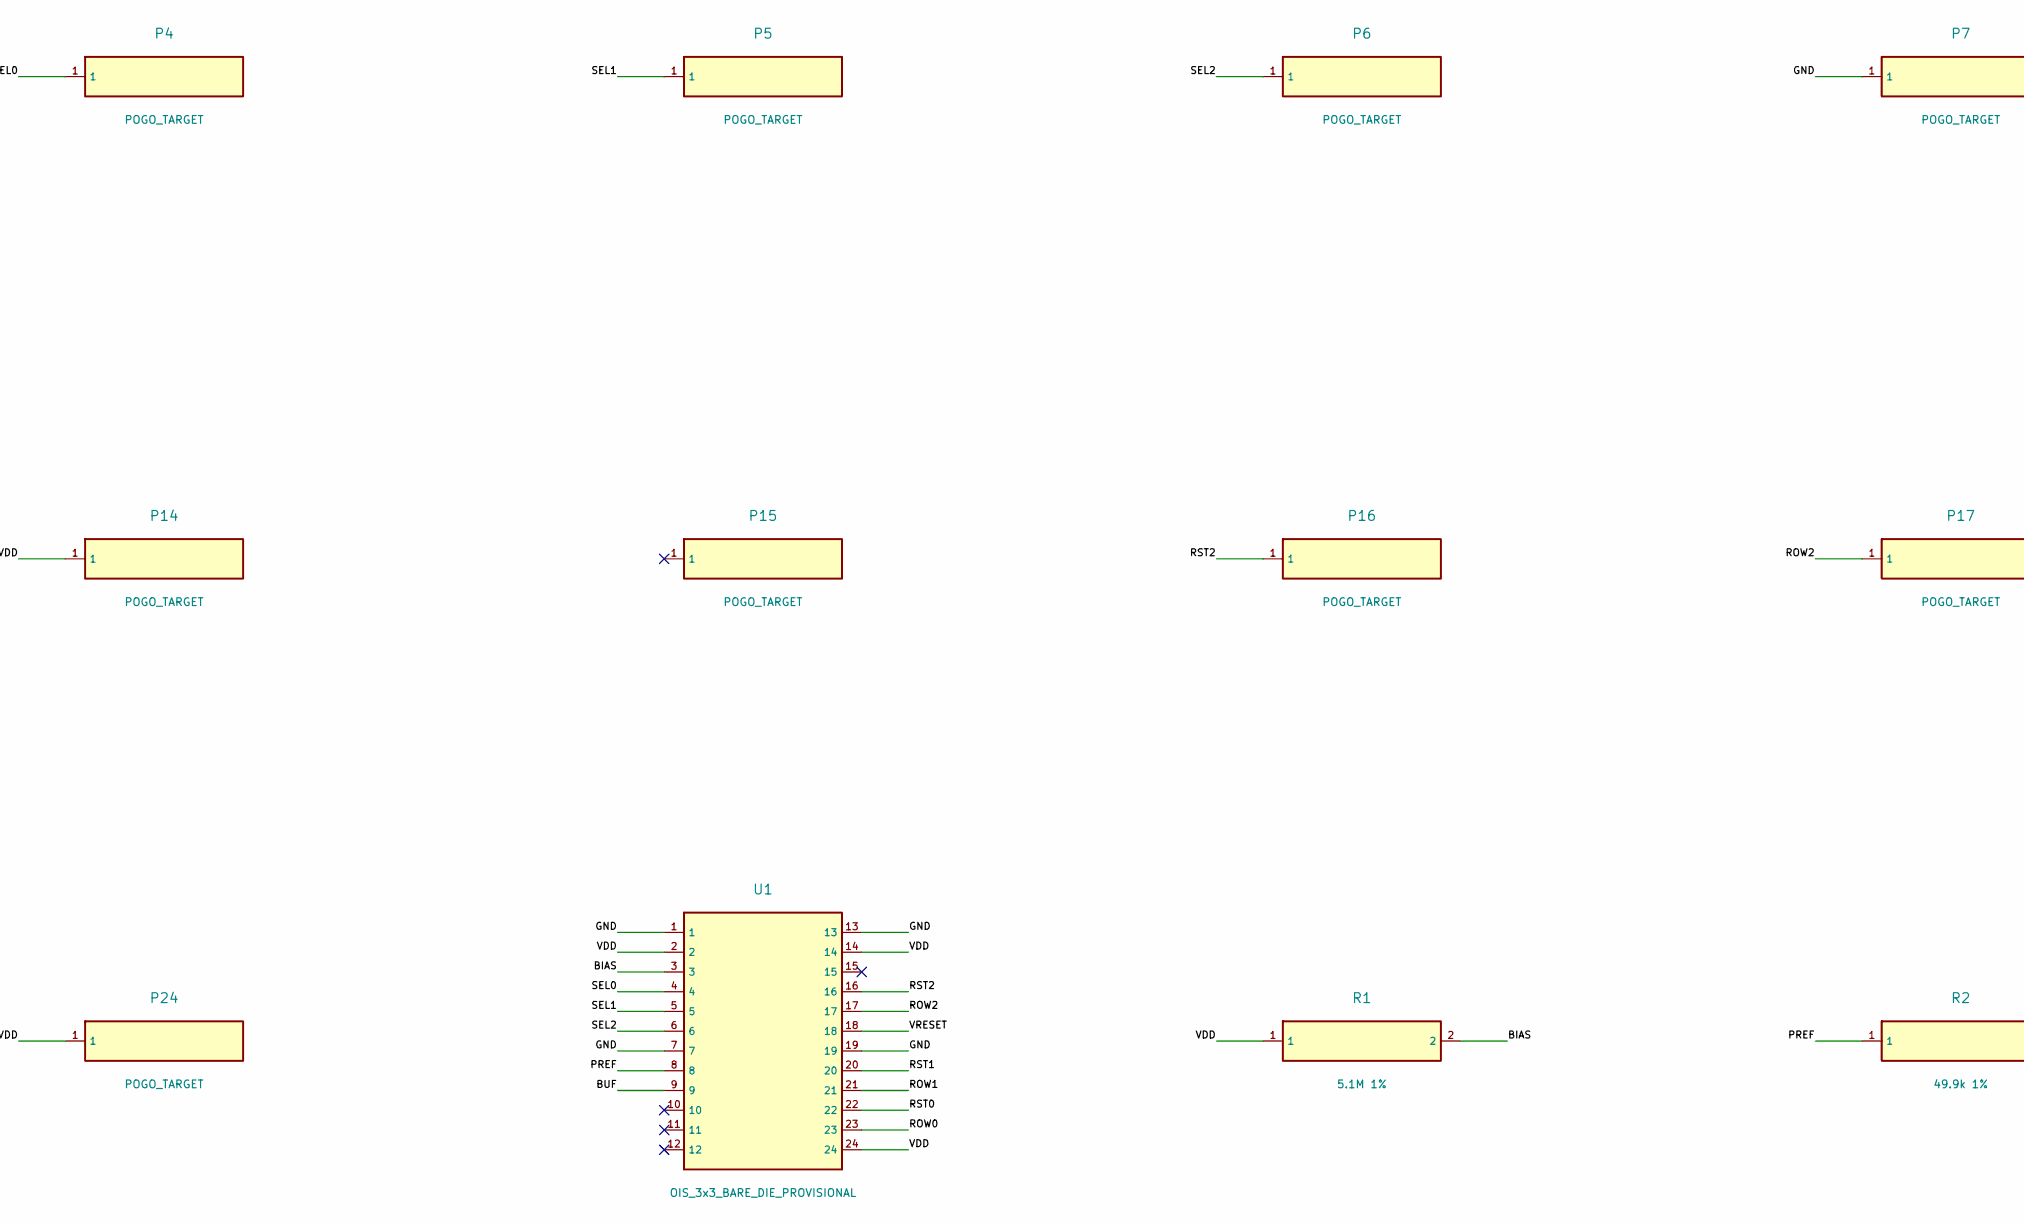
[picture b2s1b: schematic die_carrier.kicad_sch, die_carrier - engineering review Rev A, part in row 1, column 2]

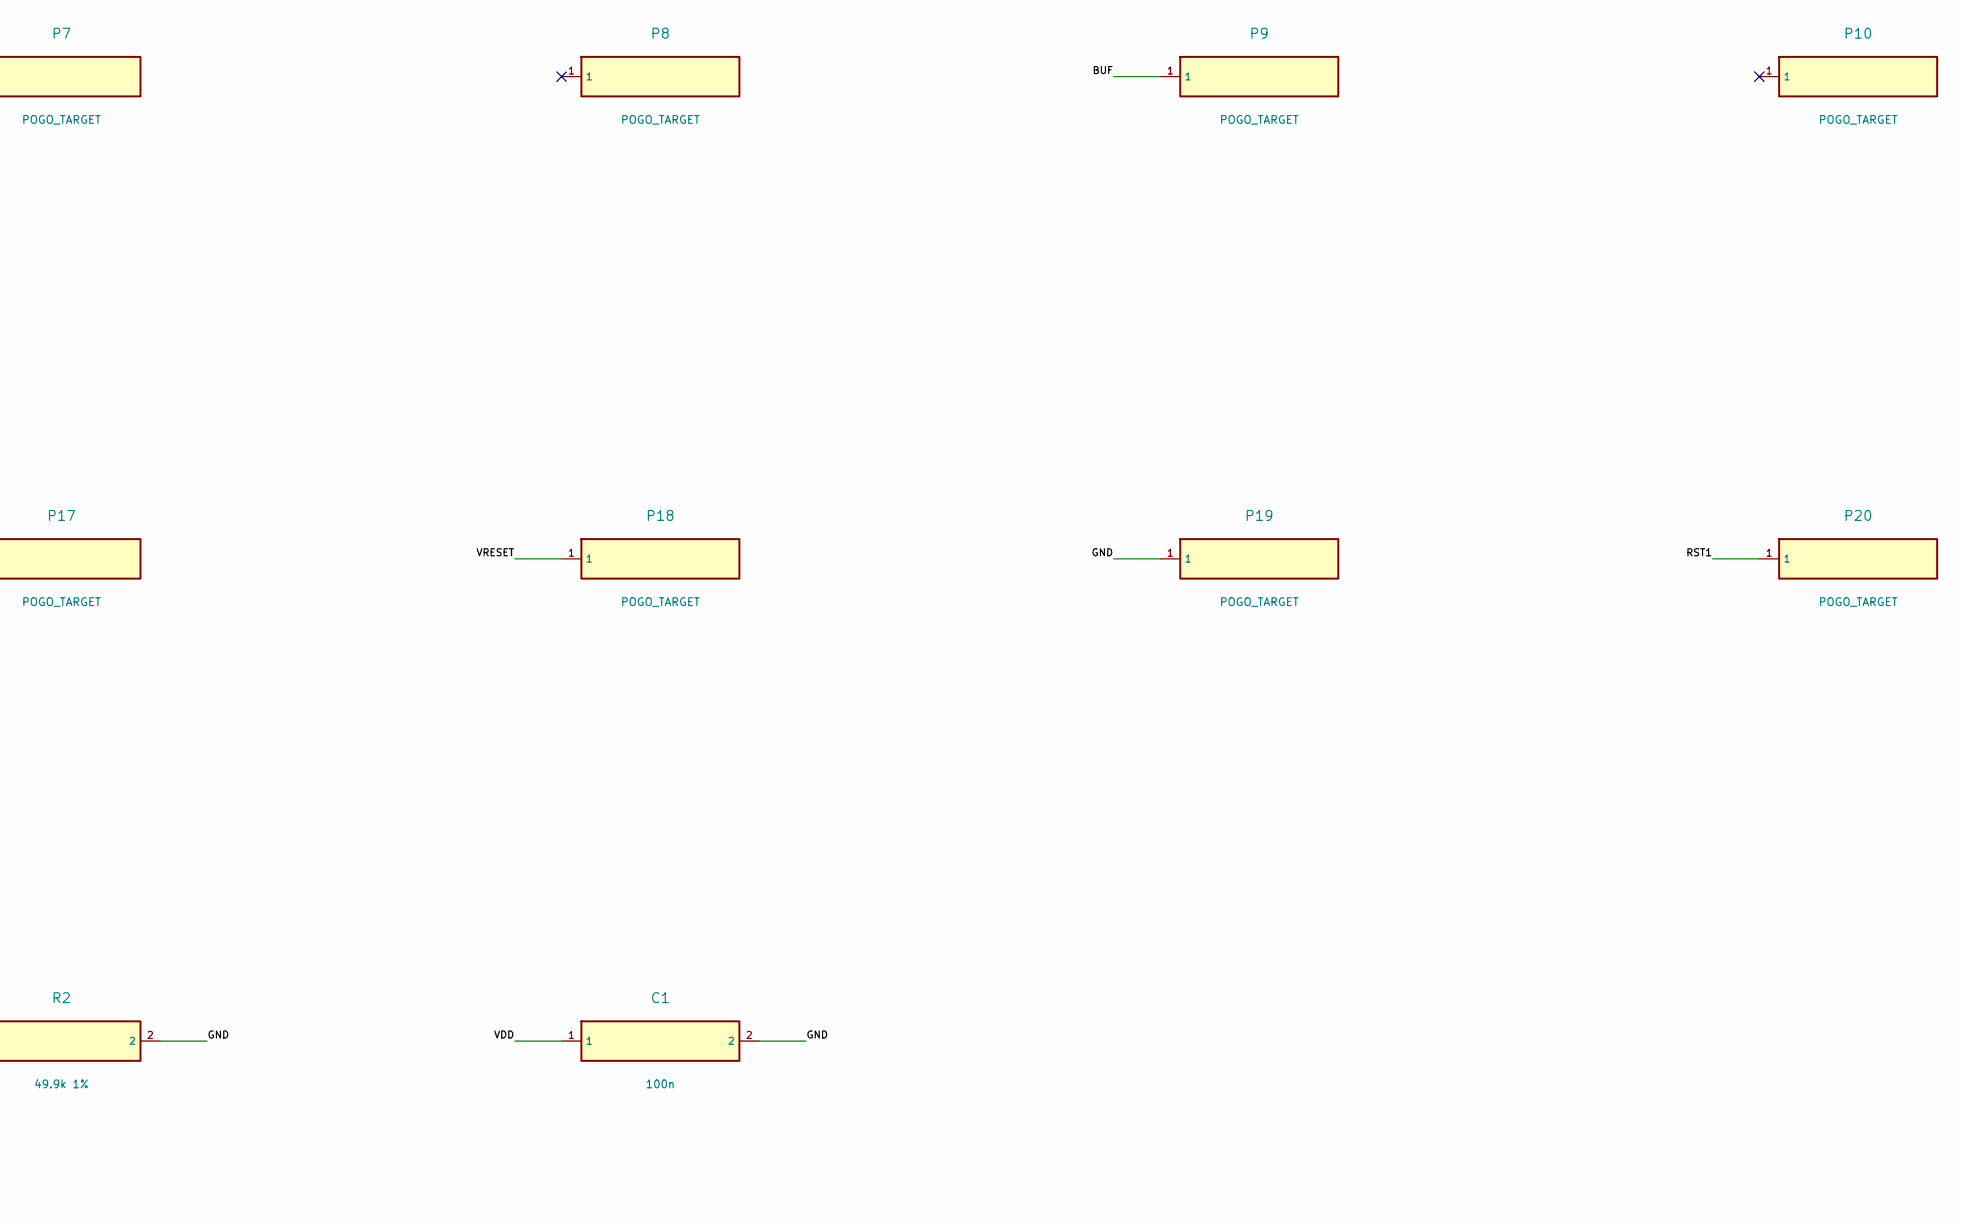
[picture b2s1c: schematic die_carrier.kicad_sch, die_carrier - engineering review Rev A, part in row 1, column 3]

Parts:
C1: 100n; Capacitor_SMD_C_0805_2012Metric
P1, P2, P3, P4, P5, P6, P7, P8, P9, P10, P11, P12, P13, P14, P15, P16, P17, P18, P19, P20, P21, P22, P23, P24: POGO_TARGET; Target_2p4
R1: 5.1M 1%; Resistor_SMD_R_0805_2012Metric
R2: 49.9k 1%; Resistor_SMD_R_0805_2012Metric
U1: OIS_3x3_BARE_DIE_PROVISIONAL; Bond_3x3_PROVISIONAL

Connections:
BIAS: R1.2, U1.3
BUF: P9.1, U1.9
GND: C1.2, P1.1, P7.1, P13.1, P19.1, R2.2, U1.1, U1.7, U1.13, U1.19
PREF: R2.1, U1.8
ROW0: P23.1, U1.23
ROW1: P21.1, U1.21
ROW2: P17.1, U1.17
RST0: P22.1, U1.22
RST1: P20.1, U1.20
RST2: P16.1, U1.16
SEL0: P4.1, U1.4
SEL1: P5.1, U1.5
SEL2: P6.1, U1.6
VDD: C1.1, P2.1, P14.1, P24.1, R1.1, U1.2, U1.14, U1.24
VRESET: P18.1, U1.18
